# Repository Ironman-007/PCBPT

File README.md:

# PCBPT (PCB Probe tester)
## The PCBPT_V3 is the latest working version (the one I showed at UIST'23).

This is a system that can help directly connect the schematic of the PCB design with test equipment (oscilloscope. etc,). When doing PCB debugging, we would need to use our hands to hold the oscilloscope probes, and our hands can not be that precise and table. Sometimes our hands are not enough, and we need to go from schematic and PCB layout back and forth to find a proper pad for the signal and place a probe on it.

The PCBPT connects the Sch with the oscilloscope. The user can choose a signal they want to check on the Sch, and the system will choose a proper pad and place a probe on the pad. Then the user can just check the output from the oscilloscope. All the user needs to do is select signals from Sch and check the output.

## PCBPT_V1.0

The first version of PCBPT is here:
https://www.media.mit.edu/projects/pcb-probe-tester/overview/

It's very rough. The machine design is not that perfect. The motor I used is [28BYJ-48](https://www.amazon.com/ELEGOO-28BYJ-48-ULN2003-Stepper-Arduino/dp/B01CP18J4A). It's very slow. The software is not that good, either. I have a separate GUI for the signal choosing. However, what I want is to choose the signal from the EDA, or make a GUI with the Sch and choose the signal from the SCH.

## PCBPT_V2.0
### Mechanical
The new machine design (I really love the Prusa color!).

### Electronics
The first version of the main control board is a modular design. Each module can control a stepper motor and a servo. Each module is an RP2040 XIAO + A4988 stepper driver. The host is an ESP32 module.

All stepper control modules are connected with the ESP32 module with I2C. The Host runs CircuitPython and is responsible for handling commands from the GUI and sending commands to each stepper control module.
This design is unnecessarily complicated compared with the function of the machine.

The second version of the main control board is a single board. One RPi Pico W module + 6 A4988 driver modules.
The probes are in vertical motion, and each probe is a triangle PCB board with a pogo pin soldered on the edge.

I use the [PCBWay](https://www.pcbway.com/) service for both the second version of the main control board and the triangle probe PCB board. The quality is good and the production is very fast.

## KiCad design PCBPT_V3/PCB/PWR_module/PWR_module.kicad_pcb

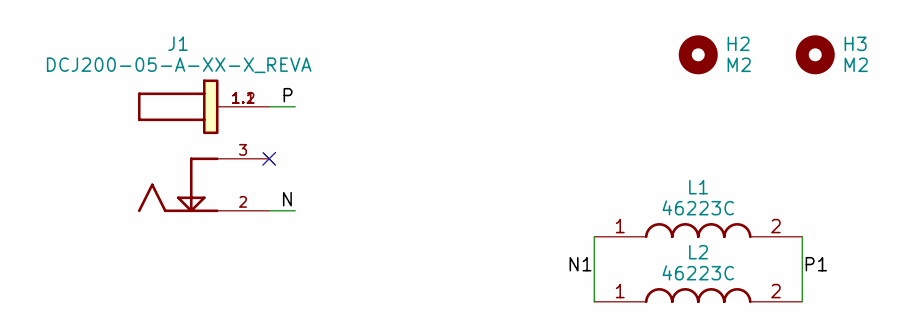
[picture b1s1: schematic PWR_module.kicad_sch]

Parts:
H2, H3: M2; MountingHole_2.2mm_M2
J1: DCJ200-05-A-XX-X_REVA; GCT_DCJ200-05-A-XX-X_REVA
L1, L2: 46223C; INDPM7373X455N; Mouser Part Number 580-46223C

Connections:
/N: J1.2
/N1: L1.1, L2.1
/P: J1.1.1, J1.1.2
/P1: L1.2, L2.2

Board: 2 copper layers, 5 parts (0 on the bottom side), 3 nets, no tracks yet.

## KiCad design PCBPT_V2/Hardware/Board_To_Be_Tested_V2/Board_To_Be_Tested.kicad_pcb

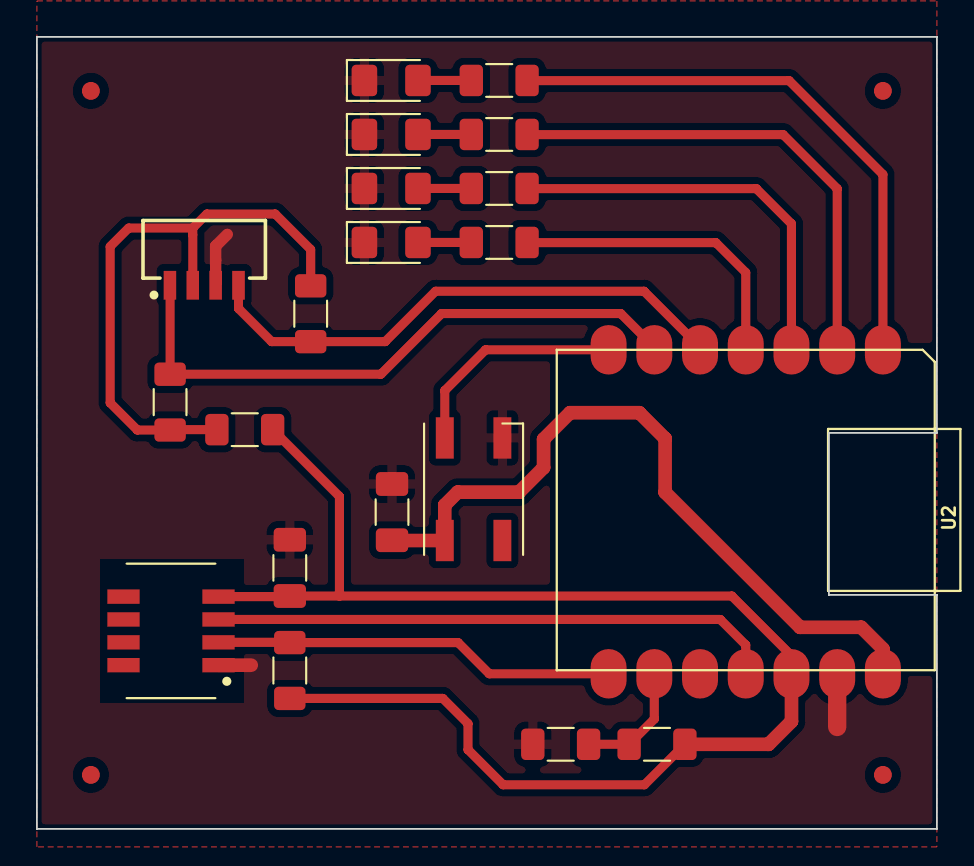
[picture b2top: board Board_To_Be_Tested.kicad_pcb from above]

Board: 2 copper layers, 50.0 x 44.0 mm, 24 parts (0 on the bottom side), 18 nets.

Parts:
C1: 0.1uF; C_1206_3216Metric_Pad1.33x1.80mm_HandSolder
C2: 10uF; C_1206_3216Metric_Pad1.33x1.80mm_HandSolder
D1: SK6812; LED_SK6812_PLCC4_5.0x5.0mm_P3.2mm
D2, D3, D4, D5: R; LED_1206_3216Metric_Pad1.42x1.75mm_HandSolder
FID1, FID2, FID3, FID4: Fiducial; Fiducial_1mm_Mask2mm
IC1: VEML7700-TR; VEML7700
R1, R2, R3, R6: 200; R_1206_3216Metric_Pad1.30x1.75mm_HandSolder
R4, R5, R7, R8, R9: 10k; R_1206_3216Metric_Pad1.30x1.75mm_HandSolder
R10: 0; R_1206_3216Metric_Pad1.30x1.75mm_HandSolder
U1: SHT15; DFN747X493X250-8N
U2: MOUDLE-SEEEDUINO-XIAO; MOUDLE14P-SMD-2.54-21X17.8MM

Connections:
+3V3: C1.1, R4.2, R7.1, R10.2, U1.4 (VDD), U2.12 (3V3)
/A0: R4.1, R5.2, U2.9 (PA7_A8_D8_SCK)
/DIN: D1.2 (DIN), U2.7 (PB08_A6_D6_TX)
/LED1: R1.2, U2.1 (PA02_A0_D0)
/LED2: R2.2, U2.2 (PA4_A1_D1)
/LED3: R3.2, U2.3 (PA10_A2_D2)
/LED4: R6.2, U2.4 (PA11_A3_D3)
/PWR: IC1.2 (VDD), R8.1, R9.2, R10.1
/SCL: IC1.1 (SCL), R8.2, U2.6 (PA9_A5_D5_SCL)
/SDA: IC1.4 (SDA), R9.1, U2.5 (PA8_A4_D4_SDA)
/SHT_CLK: U1.3 (SCK), U2.11 (PA6_A10_D10_MOSI)
/SHT_DATA: R7.2, U1.2 (DATA), U2.8 (PB09_A7_D7_RX)
GND: C1.2, C2.2, D1.1 (VSS), D2.1 (K), D3.1 (K), D4.1 (K), D5.1 (K), IC1.3 (GND), R5.1, U1.1 (GND), U2.13 (GND)
unnamed: D2.2 (A), R1.1
unnamed: D3.2 (A), R2.1
unnamed: D4.2 (A), R3.1
unnamed: D5.2 (A), R6.1
VBUS: C2.1, D1.3 (VDD), U2.14 (5V)

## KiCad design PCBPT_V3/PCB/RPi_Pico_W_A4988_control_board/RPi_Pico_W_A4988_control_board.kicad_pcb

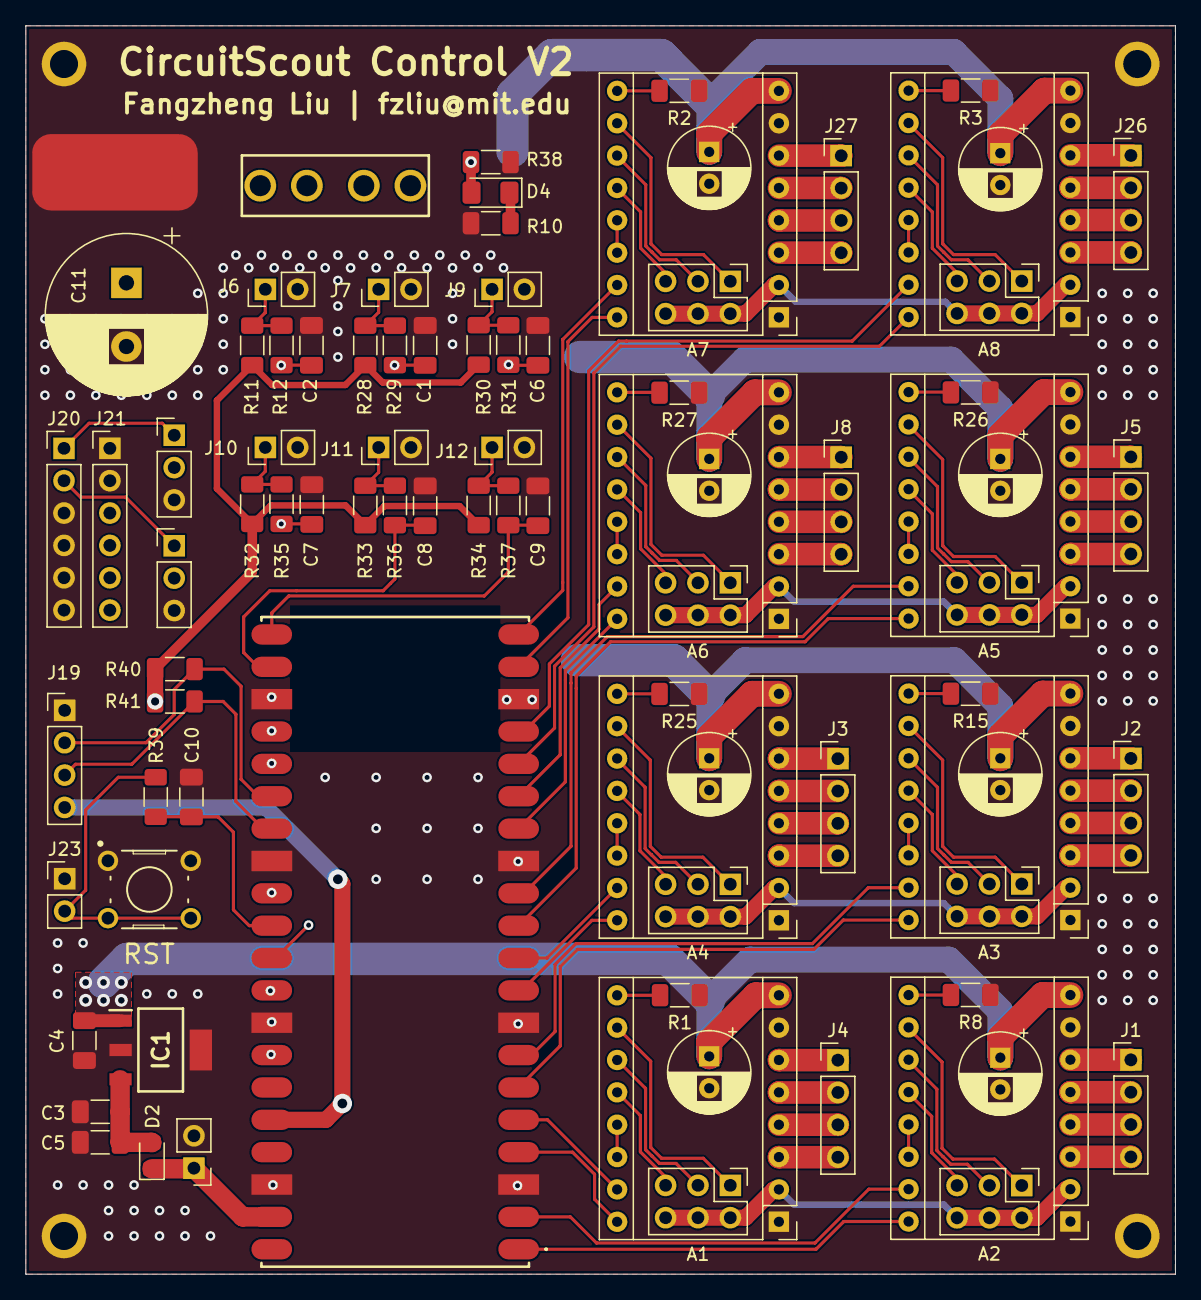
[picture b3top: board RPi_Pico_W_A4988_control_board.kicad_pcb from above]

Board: 4 copper layers, 90.2 x 98.0 mm, 93 parts (1 on the bottom side), 113 nets.

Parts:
A1, A2, A3, A4, A5, A6, A7, A8: Pololu_Breakout_A4988; Pololu_Breakout-16_15.2x20.3mm
C1, C2, C6, C7, C8, C9, C10: 0.01uF; C_1206_3216Metric_Pad1.33x1.80mm_HandSolder
C3: 22uF; C_1206_3216Metric_Pad1.33x1.80mm_HandSolder
C4: 0.47uF; C_1206_3216Metric_Pad1.33x1.80mm_HandSolder
C5: 0.1uF; C_1206_3216Metric_Pad1.33x1.80mm_HandSolder
C11: 470uF; CP_Radial_D12.5mm_P5.00mm
C12, C13, C14, C15, C16, C17, C18, C19: 100uF; CP_Radial_D6.3mm_P2.50mm
D2: Schottky; D_0805_2012Metric_Pad1.15x1.40mm_HandSolder
D4: LED_Small_Filled; LED_1206_3216Metric_Pad1.42x1.75mm_HandSolder
H1, H2, H3, H4: M2; MountingHole_2.2mm_M2_ISO7380_Pad
IC1: UA78M05IDCYR; SOT230P700X180-4N
IC2: RASPBERRY_PI_PICO_W; RASPBERRYPIPICOW
J1, J2, J3, J4, J5, J8, J19, J26, J27: Limit Switch; PinHeader_1x04_P2.54mm_Vertical
J6, J7, J9, J10, J11, J12, J22, J23: Limit Switch; PinHeader_1x02_P2.54mm_Vertical
J13, J14, J15, J16, J17, J18, J24, J25: Conn_02x03_Odd_Even; PinHeader_2x03_P2.54mm_Vertical
J20, J21: Conn_01x06_Pin; PinHeader_1x06_P2.54mm_Vertical
J28, J29: Conn_01x03_Pin; PinHeader_1x03_P2.54mm_Vertical
J30, J31: pin; conn_SMD_15mmx5mm
R1, R2, R3, R8, R11, R15, R25, R26, R27, R28, R30, R32, R33, R34, R40, R41: 10K; R_1206_3216Metric_Pad1.30x1.75mm_HandSolder
R10: 10k; R_1206_3216Metric_Pad1.30x1.75mm_HandSolder
R12, R29, R31, R35, R36, R37, R39: 100; R_1206_3216Metric_Pad1.30x1.75mm_HandSolder
R38: 100K; R_1206_3216Metric_Pad1.30x1.75mm_HandSolder
SW1: SW_MEC_5E; SW_B3F-1000
U1: 3544-2

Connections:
1A_1: A1.4 (1A), J4.3
1A_2: A2.4 (1A), J1.3
1A_3: A3.4 (1A), J2.3
1A_4: A4.4 (1A), J3.3
1A_5: A5.4 (1A), J5.3
1A_6: A6.4 (1A), J8.3
1A_7: A7.4 (1A), J27.3
1A_8: A8.4 (1A), J26.3
1B_1: A1.3 (1B), J4.4
1B_2: A2.3 (1B), J1.4
1B_3: A3.3 (1B), J2.4
1B_4: A4.3 (1B), J3.4
1B_5: A5.3 (1B), J5.4
1B_6: A6.3 (1B), J8.4
1B_7: A7.3 (1B), J27.4
1B_8: A8.3 (1B), J26.4
2A_1: A1.5 (2A), J4.2
2A_2: A2.5 (2A), J1.2
2A_3: A3.5 (2A), J2.2
2A_4: A4.5 (2A), J3.2
2A_5: A5.5 (2A), J5.2
2A_6: A6.5 (2A), J8.2
2A_7: A7.5 (2A), J27.2
2A_8: A8.5 (2A), J26.2
2B_1: A1.6 (2B), J4.1
2B_2: A2.6 (2B), J1.1
2B_3: A3.6 (2B), J2.1
2B_4: A4.6 (2B), J3.1
2B_5: A5.6 (2B), J5.1
2B_6: A6.6 (2B), J8.1
2B_7: A7.6 (2B), J27.1
2B_8: A8.6 (2B), J26.1
+3V3: A1.2 (VDD), A2.2 (VDD), A3.2 (VDD), A4.2 (VDD), A5.2 (VDD), A6.2 (VDD), A7.2 (VDD), A8.2 (VDD), IC2.36 (3V3(OUT)), J13.2, J13.4, J13.6, J14.2, J14.4, J14.6, J15.2, J15.4, J15.6, J16.2, J16.4, J16.6, J17.2, J17.4, J17.6, J18.2, J18.4, J18.6, J19.4, J21.5, J21.6, J24.2, J24.4, J24.6, J25.2, J25.4, J25.6, R11.1, R28.1, R30.1, R32.1, R33.1, R34.1, R40.1, R41.1
+5V: C3.1, C5.1, D2.2 (A), IC1.3 (OUT)
+12V: C11.1, J30.1, U1.1, U1.2
/PicoW RP2040/~RST: C10.1, IC2.30 (RUN), R39.1
DIR_1: A1.16 (DIR), IC2.4 (I2C1_SDA_/SPI0_SCK/GP2)
DIR_2: A2.16 (DIR), IC2.1 (UART0_TX/I2C0_SDA_/SPI0_RX/GP0)
DIR_3: A3.16 (DIR), IC2.6 (UART1_TX/I2C0_SDA_/SPI0_RX/GP4)
DIR_4: A4.16 (DIR), IC2.9 (I2C1_SDA_/SPI0_SCK/GP6)
DIR_5: A5.16 (DIR), IC2.11 (UART1_TX/I2C0_SDA_/SPI1_RX/GP8)
DIR_6: A6.16 (DIR), IC2.14 (I2C1_SDA_/SPI1__SCK/GP10)
DIR_7: A7.16 (DIR), IC2.19 (I2C1_SDA/SPI1_SCK/GP14)
DIR_8: A8.16 (DIR), IC2.16 (UART0_TX/I2C0_SDA_/SPI1_RX_/GP12)
GND: A1.1 (GND), A1.7 (GND), A2.1 (GND), A2.7 (GND), A3.1 (GND), A3.7 (GND), A4.1 (GND), A4.7 (GND), A5.1 (GND), A5.7 (GND), A6.1 (GND), A6.7 (GND), A7.1 (GND), A7.7 (GND), A8.1 (GND), A8.7 (GND), C1.2, C2.2, C3.2, C4.2, C5.2, C6.2, C7.2, C8.2, C9.2, C10.2, C11.2, C12.2, C13.2, C14.2, C15.2, C16.2, C17.2, C18.2, C19.2, H1.1, H2.1, H3.1, H4.1, IC1.2 (GND_1), IC1.4 (GND_2), IC2.3 (GND_1), IC2.8 (GND_2), IC2.13 (GND_3), IC2.18 (GND_4), IC2.23 (GND_5), IC2.28 (GND_6), IC2.33 (GND/AGND), IC2.38 (GND_7), J6.2, J7.2, J9.2, J10.2, J11.2, J12.2, J19.1, J20.3, J20.4, J20.5, J20.6, J21.1, J21.2, J22.2, J23.1, J28.3, J29.3, J31.1, R1.2, R2.2, R3.2, R8.2, R10.2, R15.2, R25.2, R26.2, R27.2, R38.2, SW1.1, SW1.2
IO27: IC2.32 (I2C1_SCL_/ADC1/GP_27), J20.1, J28.1
IO28: IC2.34 (GP28/ADC2), J20.2, J29.1
LIMIT_SW_1: C2.1, IC2.29 (GP22), R12.1
LIMIT_SW_2: C1.1, IC2.25 (I2C1_SCL/_SPI0_TX/GP19), R29.1
LIMIT_SW_3: C6.1, IC2.24 (I2C1_SDA/_SPI0_SCK/GP18), R31.1
LIMIT_SW_4: C7.1, IC2.31 (I2C1_SDA/ADC0/GP26), R35.1
LIMIT_SW_5: C8.1, IC2.22 (UART0_RX/I2C0_SCL/SPIO_CSN/GP17), R36.1
LIMIT_SW_6: C9.1, IC2.21 (UART0_TX/I2C0_SDA_/SPI0_RX_/GP16), R37.1
MS1_1: A1.10 (MS1), J13.1
MS1_2: A2.10 (MS1), J14.1
MS1_3: A3.10 (MS1), J15.1
MS1_4: A4.10 (MS1), J16.1
MS1_5: A5.10 (MS1), J17.1
MS1_6: A6.10 (MS1), J18.1
MS1_7: A7.10 (MS1), J24.1
MS1_8: A8.10 (MS1), J25.1
MS2_1: A1.11 (MS2), J13.3
MS2_2: A2.11 (MS2), J14.3
MS2_3: A3.11 (MS2), J15.3
MS2_4: A4.11 (MS2), J16.3
MS2_5: A5.11 (MS2), J17.3
MS2_6: A6.11 (MS2), J18.3
MS2_7: A7.11 (MS2), J24.3
MS2_8: A8.11 (MS2), J25.3
MS3_1: A1.12 (MS3), J13.5
MS3_2: A2.12 (MS3), J14.5
MS3_3: A3.12 (MS3), J15.5
MS3_4: A4.12 (MS3), J16.5
MS3_5: A5.12 (MS3), J17.5
MS3_6: A6.12 (MS3), J18.5
MS3_7: A7.12 (MS3), J24.5
MS3_8: A8.12 (MS3), J25.5
unnamed: A1.9 (~ENABLE), R1.1
unnamed: A1.13 (~RESET), A1.14 (~SLEEP)
unnamed: A2.9 (~ENABLE), R8.1
unnamed: A2.13 (~RESET), A2.14 (~SLEEP)
unnamed: A3.9 (~ENABLE), R15.1
unnamed: A3.13 (~RESET), A3.14 (~SLEEP)
unnamed: A4.9 (~ENABLE), R25.1
unnamed: A4.13 (~RESET), A4.14 (~SLEEP)
unnamed: A5.9 (~ENABLE), R26.1
unnamed: A5.13 (~RESET), A5.14 (~SLEEP)
unnamed: A6.9 (~ENABLE), R27.1
unnamed: A6.13 (~RESET), A6.14 (~SLEEP)
unnamed: A7.9 (~ENABLE), R2.1
unnamed: A7.13 (~RESET), A7.14 (~SLEEP)
unnamed: A8.9 (~ENABLE), R3.1
unnamed: A8.13 (~RESET), A8.14 (~SLEEP)
unnamed: D4.1 (K), R10.1
unnamed: J6.1, R11.2, R12.2
unnamed: J7.1, R28.2, R29.2
unnamed: J9.1, R30.2, R31.2
unnamed: J10.1, R32.2, R35.2
unnamed: J11.1, R33.2, R36.2
unnamed: J12.1, R34.2, R37.2
unnamed: J23.2, R39.2, SW1.3 (K), SW1.4 (A)
SCL: IC2.27 (I2C0_SCL/GP21), J19.3, R41.2
SDA: IC2.26 (I2C0_SDA/GP20), J19.2, R40.2
STEP_1: A1.15 (STEP), IC2.5 (I2C0_SCL_/SPI0_TX/GP3)
STEP_2: A2.15 (STEP), IC2.2 (UART0_RX/I2C0_SCL_/SPI0_CSN/GP1)
STEP_3: A3.15 (STEP), IC2.7 (UART1_RX/I2C0_SCL_/SPI0_CSN/GP5)
STEP_4: A4.15 (STEP), IC2.10 (I2C1_SCL_/SPI0_TX/GP7)
STEP_5: A5.15 (STEP), IC2.12 (UART1_RX/I2C0_SCL_/SPI1_CSN/GP9)
STEP_6: A6.15 (STEP), IC2.15 (I2C1_SCL_/SPI1__TX/GP11)
STEP_7: A7.15 (STEP), IC2.20 (I2C1_SCL/SPI1_TX/GP15)
STEP_8: A8.15 (STEP), IC2.17 (UART0_RX/I2C0_SCL_/SPI1_CSN/GP13)
VPP: A1.8 (VMOT), A2.8 (VMOT), A3.8 (VMOT), A4.8 (VMOT), A5.8 (VMOT), A6.8 (VMOT), A7.8 (VMOT), A8.8 (VMOT), C4.1, C12.1, C13.1, C14.1, C15.1, C16.1, C17.1, C18.1, C19.1, D4.2 (A), IC1.1 (IN), R38.1, U1.3, U1.4
VSYS: D2.1 (K), IC2.39 (VSYS), J21.3, J21.4, J22.1, J28.2, J29.2

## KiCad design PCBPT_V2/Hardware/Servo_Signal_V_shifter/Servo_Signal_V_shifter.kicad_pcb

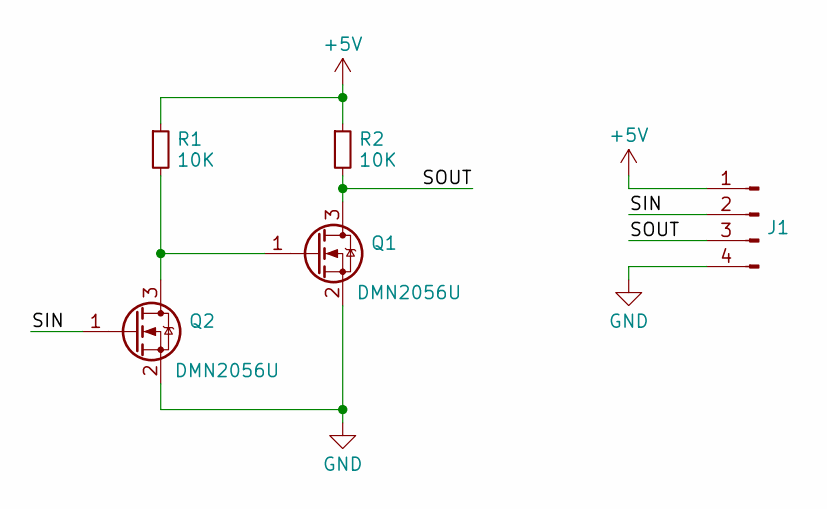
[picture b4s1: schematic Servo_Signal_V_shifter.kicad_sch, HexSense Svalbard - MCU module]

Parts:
J1: Conn_01x04_Pin; Harwin_M20-89004xx_1x04_P2.54mm_Horizontal
Q1, Q2: DMN2056U; SOT-23
R1, R2: 10K; R_1206_3216Metric_Pad1.30x1.75mm_HandSolder

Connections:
+5V: J1.1, R1.1, R2.1
/SIN: J1.2, Q2.1 (G)
/SOUT: J1.3, Q1.3 (D), R2.2
GND: J1.4, Q1.2 (S), Q2.2 (S)
unnamed: Q1.1 (G), Q2.3 (D), R1.2

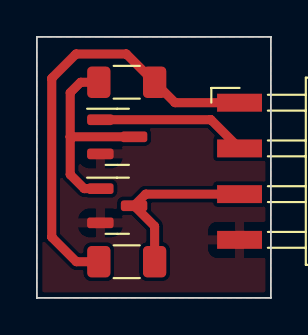
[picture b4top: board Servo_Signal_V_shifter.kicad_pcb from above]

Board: 2 copper layers, 13.0 x 14.5 mm, 5 parts (0 on the bottom side), 5 nets.

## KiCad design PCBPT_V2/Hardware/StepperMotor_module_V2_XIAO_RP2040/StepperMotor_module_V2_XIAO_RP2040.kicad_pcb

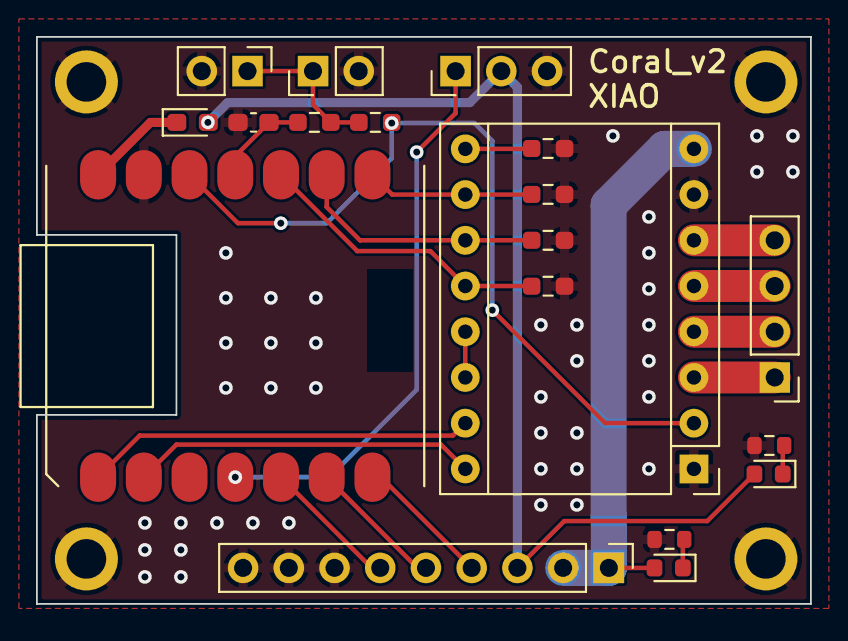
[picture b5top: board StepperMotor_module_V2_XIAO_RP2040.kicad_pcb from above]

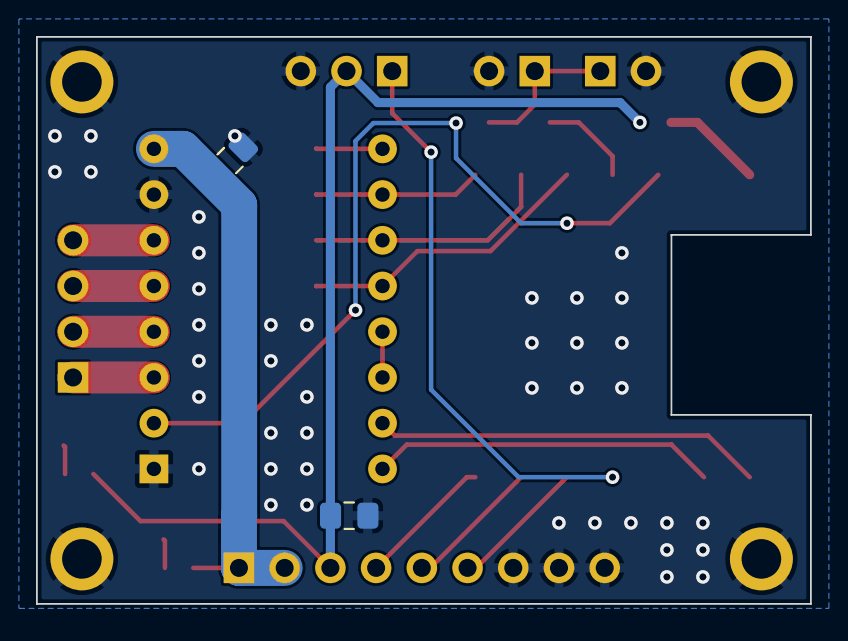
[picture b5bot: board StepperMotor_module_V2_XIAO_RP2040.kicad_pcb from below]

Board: 2 copper layers, 43.0 x 31.5 mm, 25 parts (2 on the bottom side), 24 nets.

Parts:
A1: Pololu_Breakout_A4988; Pololu_Breakout-16_15.2x20.3mm
C1, C3: 0.1uF; C_0805_2012Metric_Pad1.18x1.45mm_HandSolder
C2: 0.01uF; C_0603_1608Metric_Pad1.08x0.95mm_HandSolder
D1, D4: LED_Small_Filled; LED_0603_1608Metric
D2: Schottky; D_0603_1608Metric_Pad1.05x0.95mm_HandSolder
H1, H2, H3, H4: M2; MountingHole_2.2mm_M2_ISO7380_Pad
J3: Servo; PinHeader_1x03_P2.54mm_Vertical
J4: Limit Switch; PinHeader_1x04_P2.54mm_Vertical
J5: Conn_01x09_Pin; PinHeader_1x09_P2.54mm_Vertical
J6, J7: Limit Switch; PinHeader_1x02_P2.54mm_Vertical
R1: 499K; R_0603_1608Metric_Pad0.98x0.95mm_HandSolder
R2, R3, R4, R11: 10K; R_0603_1608Metric_Pad0.98x0.95mm_HandSolder
R8, R10: 10k; R_0603_1608Metric
R12: 100; R_0603_1608Metric_Pad0.98x0.95mm_HandSolder
U1: MOUDLE-SEEEDUINO-XIAO; MOUDLE14P-SMD-2.54-21X17.8MM

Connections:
1A: A1.4 (1A), J4.2
1B: A1.3 (1B), J4.1
2A: A1.5 (2A), J4.3
2B: A1.6 (2B), J4.4
+3V3: A1.2 (VDD), R11.1, U1.12 (3V3)
/A4988_Module/M_EN: A1.9 (~ENABLE), R1.1
DIR: A1.16 (DIR), U1.2 (PA4_A1_D1)
GND: A1.1 (GND), A1.7 (GND), C1.2, C2.2, C3.2, H1.1, H2.1, H3.1, H4.1, J3.3, J5.7, J5.8, J5.9, J6.2, J7.2, R1.2, R2.2, R3.2, R4.2, R8.2, R10.2, U1.13 (GND)
GPIO: J5.4, U1.7 (PB08_A6_D6_TX)
LIMIT_SW_0: C2.1, R12.1, U1.11 (PA6_A10_D10_MOSI)
MS1: A1.10 (MS1), R2.1, U1.8 (PB09_A7_D7_RX)
MS2: A1.11 (MS2), R3.1, U1.9 (PA7_A8_D8_SCK)
MS3: A1.12 (MS3), R4.1, U1.10 (PA5_A9_D9_MISO)
unnamed: A1.13 (~RESET), A1.14 (~SLEEP)
unnamed: D1.1 (K), R8.1
unnamed: D2.1 (K), U1.14 (5V)
unnamed: D4.1 (K), R10.1
unnamed: J6.1, J7.1, R11.2, R12.2
PWM_S: J3.1, U1.4 (PA11_A3_D3)
SCL: J5.5, U1.6 (PA9_A5_D5_SCL)
SDA: J5.6, U1.5 (PA8_A4_D4_SDA)
STEP: A1.15 (STEP), U1.1 (PA02_A0_D0)
VCC: C3.1, D1.2 (A), D2.2 (A), J3.2, J5.3
VPP: A1.8 (VMOT), C1.1, D4.2 (A), J5.1, J5.2

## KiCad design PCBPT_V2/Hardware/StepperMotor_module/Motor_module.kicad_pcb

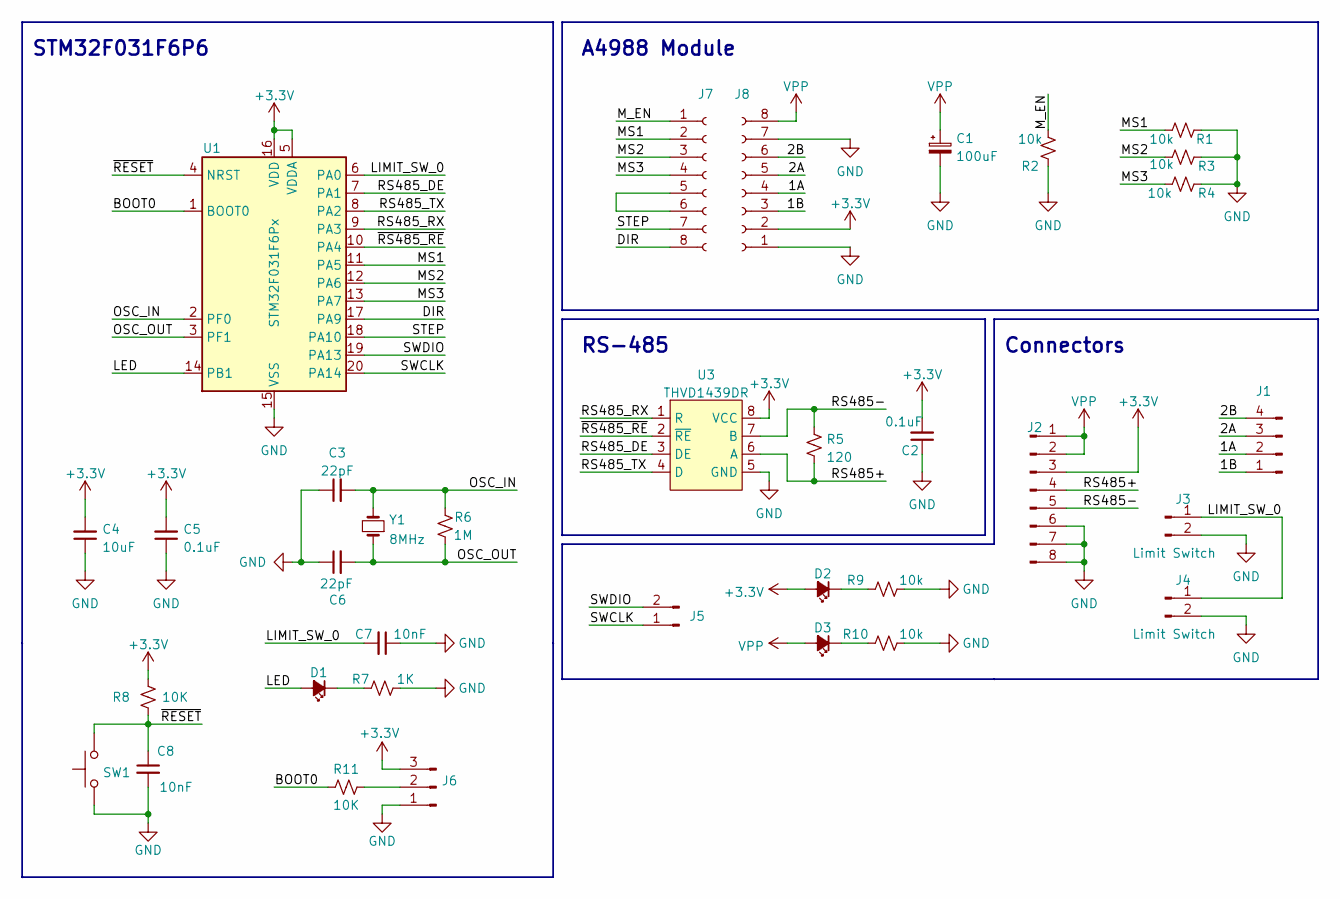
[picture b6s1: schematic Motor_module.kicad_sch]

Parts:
C1: 100uF; CP_Radial_D5.0mm_P2.50mm
C2, C5: 0.1uF; C_0603_1608Metric
C3, C6: 22pF; C_0603_1608Metric
C4: 10uF; C_0603_1608Metric
C7, C8: 10nF; C_0402_1005Metric
D1, D2, D3: LED_Small_Filled; LED_0603_1608Metric
J1: Limit Switch; PinHeader_1x04_P2.54mm_Vertical
J2: Limit Switch; PinHeader_1x08_P2.54mm_Horizontal
J3, J4: Limit Switch; JST_EH_B2B-EH-A_1x02_P2.50mm_Vertical
J5: Conn_01x08_Male; PinHeader_1x02_P2.54mm_Vertical
J6: Conn_01x04_Male; PinHeader_1x03_P2.54mm_Vertical
J7, J8: Conn_01x08_Female; PinSocket_1x08_P2.54mm_Vertical
R1, R2, R3, R4, R9, R10: 10k; R_0603_1608Metric
R5: 120; R_0603_1608Metric
R6: 1M; R_0603_1608Metric
R7: 1K; R_0603_1608Metric
R8, R11: 10K; R_0603_1608Metric
SW1: SW_Push; SW_Push_1P1T_NO_CK_KMR2
U1: STM32F031F6Px; TSSOP-20_4.4x6.5mm_P0.65mm
U3: THVD1439DR; PowerIntegrations_SO-8
Y1: 8MHz; Crystal_HC18-U_Vertical

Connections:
+3V3: C2.2, C4.2, C5.2, D2.2 (A), J2.3, J6.3, J8.2, R8.2, U1.5 (VDDA), U1.16 (VDD), U3.8 (VCC)
/1A: J1.2, J8.4
/1B: J1.1, J8.3
/2A: J1.3, J8.5
/2B: J1.4, J8.6
/BOOT0: R11.1, U1.1 (BOOT0)
/DIR: J7.8, U1.17 (PA9)
/LED: D1.2 (A), U1.14 (PB1)
/LIMIT_SW_0: C7.2, J3.1, J4.1, U1.6 (PA0)
/MS1: J7.2, R1.1, U1.11 (PA5)
/MS2: J7.3, R3.1, U1.12 (PA6)
/MS3: J7.4, R4.1, U1.13 (PA7)
/M_EN: J7.1, R2.1
/OSC_IN: C3.2, R6.2, U1.2 (PF0), Y1.2
/OSC_OUT: C6.2, R6.1, U1.3 (PF1), Y1.1
/RS485+: J2.4, R5.2, U3.6 (A)
/RS485-: J2.5, R5.1, U3.7 (B)
/RS485_DE: U1.7 (PA1), U3.3 (DE)
/RS485_RX: U1.9 (PA3), U3.1 (R)
/RS485_TX: U1.8 (PA2), U3.4 (D)
/STEP: J7.7, U1.18 (PA10)
/SWCLK: J5.1, U1.20 (PA14)
/SWDIO: J5.2, U1.19 (PA13)
/~RESET: C8.1, R8.1, SW1.2, U1.4 (NRST)
/~RS485_RE: U1.10 (PA4), U3.2 (~RE)
GND: C1.2, C2.1, C3.1, C4.1, C5.1, C6.1, C7.1, C8.2, J2.6, J2.7, J2.8, J3.2, J4.2, J6.1, J8.1, J8.7, R1.2, R2.2, R3.2, R4.2, R7.2, R9.2, R10.2, SW1.1, U1.15 (VSS), U3.5 (GND)
unnamed: D1.1 (K), R7.1
unnamed: D2.1 (K), R9.1
unnamed: D3.1 (K), R10.1
unnamed: J6.2, R11.2
unnamed: J7.5, J7.6
VPP: C1.1, D3.2 (A), J2.1, J2.2, J8.8

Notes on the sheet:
STM32F031F6P6
RS-485
A4988 Module
Connectors

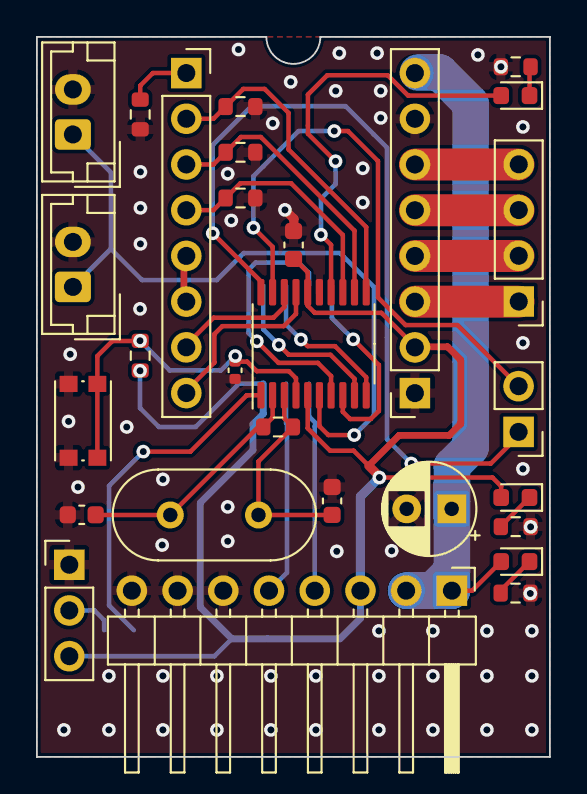
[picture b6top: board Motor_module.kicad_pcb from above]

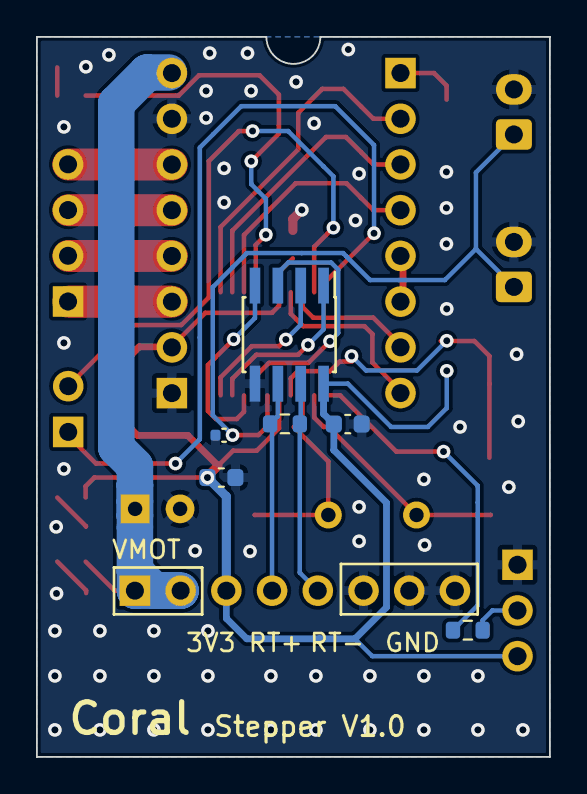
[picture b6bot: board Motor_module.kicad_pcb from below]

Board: 2 copper layers, 28.5 x 40.0 mm, 34 parts (6 on the bottom side), 32 nets.

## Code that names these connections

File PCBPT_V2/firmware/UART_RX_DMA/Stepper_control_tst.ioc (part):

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Mcu.Name=STM32F031F(4-6)Px
Mcu.Package=TSSOP20
Mcu.UserName=STM32F031F6Px
PA0.GPIOParameters=GPIO_Label
PA0.GPIO_Label=PIN_LIMIT_SW
PA0.Signal=GPIO_Input
PA1.GPIOParameters=GPIO_Label
PA1.GPIO_Label=PIN_RS485_DE
PA1.Signal=GPIO_Output
PA10.GPIOParameters=GPIO_Label
PA10.GPIO_Label=PIN_STEP
PA10.Signal=GPIO_Output
PA13.Mode=Serial_Wire
PA13.Signal=SYS_SWDIO
PA14.Mode=Serial_Wire
PA14.Signal=SYS_SWCLK
PA2.Mode=Asynchronous
PA2.Signal=USART1_TX
PA3.Mode=Asynchronous
PA3.Signal=USART1_RX
PA4.GPIOParameters=GPIO_Label
PA4.GPIO_Label=PIN_RS495_RE
PA4.Signal=GPIO_Output
PA5.GPIOParameters=GPIO_Label
PA5.GPIO_Label=PIN_MS1
PA5.Signal=GPIO_Output
PA6.GPIOParameters=GPIO_Label
PA6.GPIO_Label=PIN_MS2
PA6.Signal=GPIO_Output
PA7.GPIOParameters=GPIO_Label
PA7.GPIO_Label=PIN_MS3
PA7.Signal=GPIO_Output
PA9.GPIOParameters=GPIO_Label
PA9.GPIO_Label=PIN_DIR
PA9.Signal=GPIO_Output
PB1.GPIOParameters=GPIO_Label
PB1.GPIO_Label=PIN_LED
PB1.Signal=GPIO_Output
PF0-OSC_IN.Mode=HSE-External-Oscillator
PF0-OSC_IN.Signal=RCC_OSC_IN
PF1-OSC_OUT.Mode=HSE-External-Oscillator
PF1-OSC_OUT.Signal=RCC_OSC_OUT
RCC.SYSCLKFreq_VALUE=32000000
RCC.SYSCLKSource=RCC_SYSCLKSOURCE_PLLCLK
board=custom

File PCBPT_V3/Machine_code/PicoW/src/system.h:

//
// Created by l1534 on 9/14/2023.
//

#ifndef __SYSTEM_H
#define __SYSTEM_H

extern void debug_info(char * output);
extern void debug_info(int output);

#define LIMIT_SW_1_PIN D22
#define LIMIT_SW_2_PIN D19
#define LIMIT_SW_3_PIN D18
#define LIMIT_SW_4_PIN D26
#define LIMIT_SW_5_PIN D17
#define LIMIT_SW_6_PIN D16

extern void pin_init(void);

#endif //PICOW_SYSTEM_H

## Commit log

2021-10-17 udated by FZ
2023-07-06 Adding first version of the interface
2023-07-19 Add pcbpt upload interface
2023-07-20 Adding kicanvas files, better UI and serial com
2023-07-28 Adding PCB view
2023-07-28 Removing textures
2023-07-28 Adding board edges
2023-08-01 2D interface and probing command
2023-08-01 Small changes
2023-08-04 Adding nav, better probing, new UI and manual port refresh
2023-08-06 Better CSS, start of README doc
